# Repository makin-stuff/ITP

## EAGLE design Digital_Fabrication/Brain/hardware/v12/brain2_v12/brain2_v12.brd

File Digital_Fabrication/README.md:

This repo has all the design files, code, and documentation for [A Nervous System](https://www.priyankamakin.com/brain) by [Priyanka Makin](https://www.priyankamakin.com/)

# How to populate brain boards

For any version, each brain board consists of a string of 80 addressable LEDs , 40 on the front and 40 on the back. This is the only component used on the whole board which makes assembly pretty straight forward!

The addressable LED footprint used in this design was made to be used with [these NeoPixels I got from Adafruit.](https://www.adafruit.com/product/4957)

The orientation of the LED matters for the communication between LEDs to work, so always double-check before soldering!

If you are building up version 1.0 of these boards (with green soldermask) there is a white silkscreen triangle indicator for pin 1 on the LED footprint. Be sure to line this silkscreen up with the pin of the LED that also has a triangle cut out of it in the package.

For a more in-depth guide to surface mount soldering with solderpaste and a stencil, feel free to check out this [blog post](https://www.priyankamakin.com/blog/itp-thesis-i-this-system-is-nervous). Happy soldering!

<table class="table table-hover table-striped table-bordered">
  <tr align="center">
    <td></td>
    <td></td>
  </tr>
  <tr align="center">
    <td>Printed circuit board (v1.0) with silkscreen</td>
    <td>Adafruit NeoPixel</td>
  </tr>
</table>

# Note 08/19/24:

As I'm writing this ReadMe I'm realizing that I misnumbered the pins in the EAGLE footprint for the NeoPixel. This is just a notation error and doesn't affect functionality. Will update EAGLE library files in future revisions.

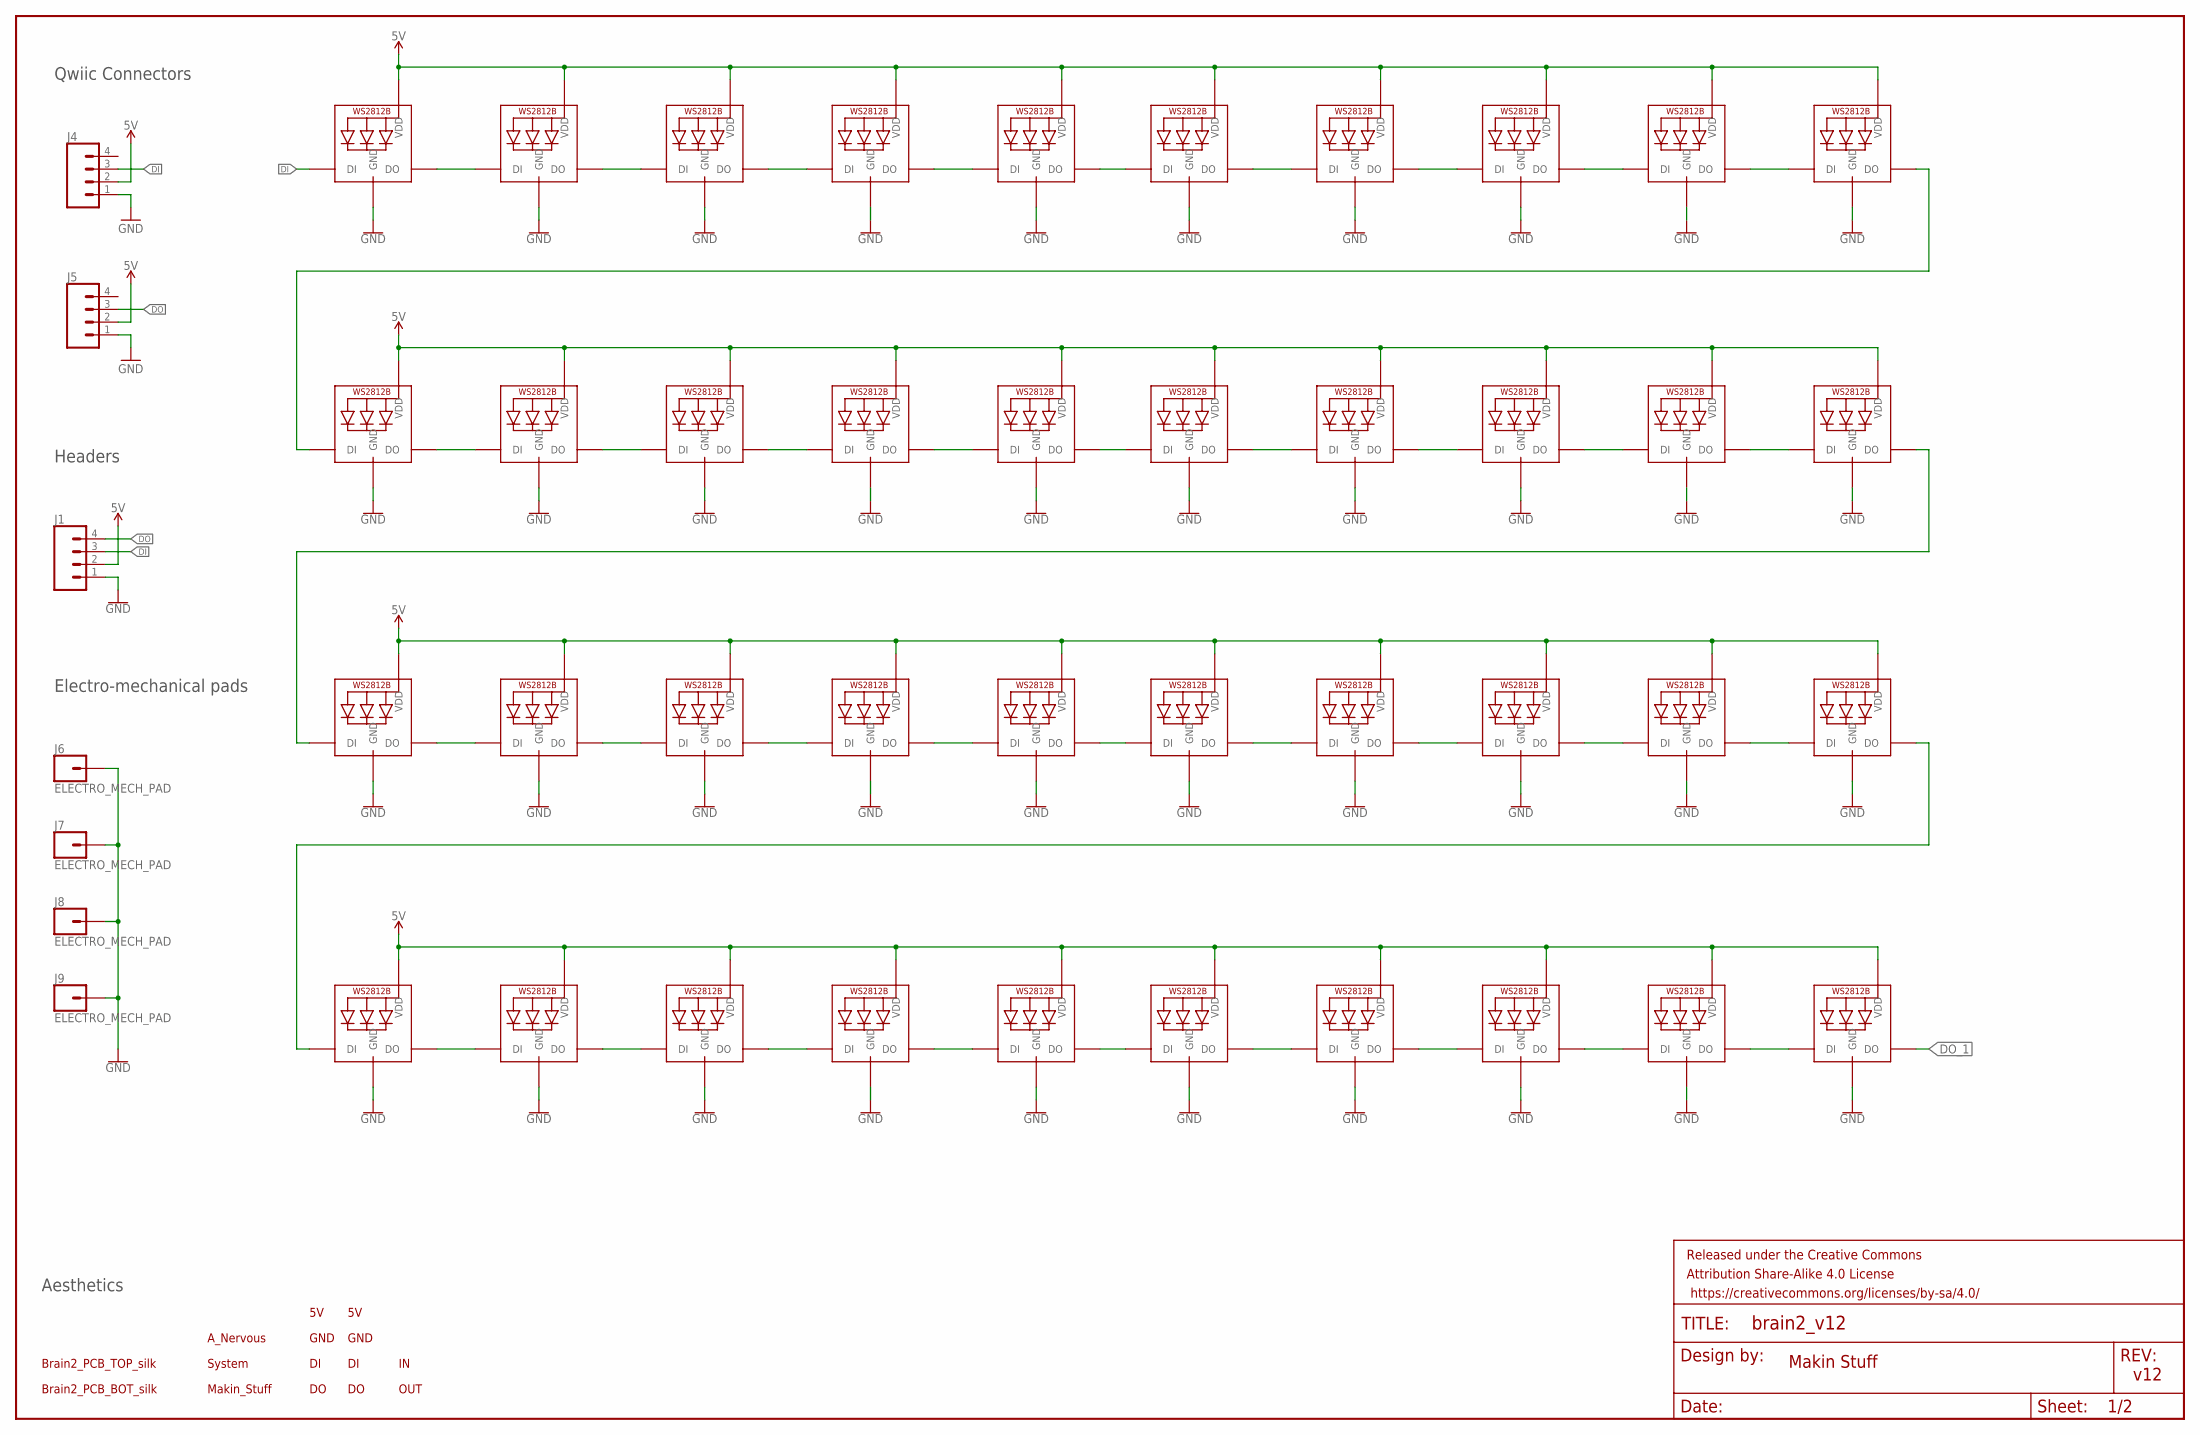
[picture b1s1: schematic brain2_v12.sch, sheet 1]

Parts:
FRAME2: FRAME-LEDGER; CREATIVE_COMMONS
J1: CONN_041X04_NO_SILK_NO_POP; 1X04_NO_SILK
J4, J5: CONN_04SMD3; JST04_1MM_RA
J6, J7, J8, J9: ELECTRO_MECH_PAD; 5X3_SOLDER_PAD
LED1, LED2, LED3, LED4, LED5, LED6, LED7, LED8, LED9, LED10, LED11, LED12, LED13, LED14, LED15, LED16, LED17, LED18, LED19, LED20, LED21, LED22, LED23, LED24, LED25, LED26, LED27, LED28, LED29, LED30, LED31, LED32, LED33, LED34, LED35, LED36, LED37, LED38, LED39, LED40: 3.5X3.5_RGB_LED3.5X3.5; 3.5X3.5_RGB_LED
U$1: A_NERVOUS0
U$2: SYSTEM1
U$3: MAKIN_STUFF2
U$4, U$5: 5V1
U$6, U$7: GND0
U$8, U$9: DI0
U$10, U$11: DO3
U$12: IN0
U$13: OUT1
U$14: BRAIN2_PCB_TOP_SILK
U$15: BRAIN2_PCB_BOT_SILK

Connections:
5V: J1.2, J4.2, J5.2, LED1.4 (VDD), LED2.4 (VDD), LED3.4 (VDD), LED4.4 (VDD), LED5.4 (VDD), LED6.4 (VDD), LED7.4 (VDD), LED8.4 (VDD), LED9.4 (VDD), LED10.4 (VDD), LED11.4 (VDD), LED12.4 (VDD), LED13.4 (VDD), LED14.4 (VDD), LED15.4 (VDD), LED16.4 (VDD), LED17.4 (VDD), LED18.4 (VDD), LED19.4 (VDD), LED20.4 (VDD), LED21.4 (VDD), LED22.4 (VDD), LED23.4 (VDD), LED24.4 (VDD), LED25.4 (VDD), LED26.4 (VDD), LED27.4 (VDD), LED28.4 (VDD), LED29.4 (VDD), LED30.4 (VDD), LED31.4 (VDD), LED32.4 (VDD), LED33.4 (VDD), LED34.4 (VDD), LED35.4 (VDD), LED36.4 (VDD), LED37.4 (VDD), LED38.4 (VDD), LED39.4 (VDD), LED40.4 (VDD); also elsewhere on the board
DI: J1.3, J4.3, LED1.3 (DI)
DO: J1.4, J5.3; also elsewhere on the board
DO_1: LED40.1 (DO); also elsewhere on the board
GND: J1.1, J4.1, J5.1, J6.P$1, J7.P$1, J8.P$1, J9.P$1, LED1.2 (GND), LED2.2 (GND), LED3.2 (GND), LED4.2 (GND), LED5.2 (GND), LED6.2 (GND), LED7.2 (GND), LED8.2 (GND), LED9.2 (GND), LED10.2 (GND), LED11.2 (GND), LED12.2 (GND), LED13.2 (GND), LED14.2 (GND), LED15.2 (GND), LED16.2 (GND), LED17.2 (GND), LED18.2 (GND), LED19.2 (GND), LED20.2 (GND), LED21.2 (GND), LED22.2 (GND), LED23.2 (GND), LED24.2 (GND), LED25.2 (GND), LED26.2 (GND), LED27.2 (GND), LED28.2 (GND), LED29.2 (GND), LED30.2 (GND), LED31.2 (GND), LED32.2 (GND), LED33.2 (GND), LED34.2 (GND), LED35.2 (GND), LED36.2 (GND), LED37.2 (GND), LED38.2 (GND), LED39.2 (GND), LED40.2 (GND); also elsewhere on the board
unnamed: LED1.1 (DO), LED2.3 (DI)
unnamed: LED2.1 (DO), LED3.3 (DI)
unnamed: LED3.1 (DO), LED4.3 (DI)
unnamed: LED4.1 (DO), LED5.3 (DI)
unnamed: LED6.1 (DO), LED7.3 (DI)
unnamed: LED7.1 (DO), LED8.3 (DI)
unnamed: LED8.1 (DO), LED9.3 (DI)
unnamed: LED9.1 (DO), LED10.3 (DI)
unnamed: LED11.1 (DO), LED12.3 (DI)
unnamed: LED5.1 (DO), LED6.3 (DI)
unnamed: LED12.1 (DO), LED13.3 (DI)
unnamed: LED13.1 (DO), LED14.3 (DI)
unnamed: LED14.1 (DO), LED15.3 (DI)
unnamed: LED16.1 (DO), LED17.3 (DI)
unnamed: LED17.1 (DO), LED18.3 (DI)
unnamed: LED18.1 (DO), LED19.3 (DI)
unnamed: LED19.1 (DO), LED20.3 (DI)
unnamed: LED15.1 (DO), LED16.3 (DI)
unnamed: LED21.1 (DO), LED22.3 (DI)
unnamed: LED22.1 (DO), LED23.3 (DI)
unnamed: LED23.1 (DO), LED24.3 (DI)
unnamed: LED24.1 (DO), LED25.3 (DI)
unnamed: LED26.1 (DO), LED27.3 (DI)
unnamed: LED27.1 (DO), LED28.3 (DI)
unnamed: LED28.1 (DO), LED29.3 (DI)
unnamed: LED29.1 (DO), LED30.3 (DI)
unnamed: LED25.1 (DO), LED26.3 (DI)
unnamed: LED31.1 (DO), LED32.3 (DI)
unnamed: LED32.1 (DO), LED33.3 (DI)
unnamed: LED33.1 (DO), LED34.3 (DI)
unnamed: LED34.1 (DO), LED35.3 (DI)
unnamed: LED36.1 (DO), LED37.3 (DI)
unnamed: LED37.1 (DO), LED38.3 (DI)
unnamed: LED38.1 (DO), LED39.3 (DI)
unnamed: LED39.1 (DO), LED40.3 (DI)
unnamed: LED35.1 (DO), LED36.3 (DI)
unnamed: LED10.1 (DO), LED11.3 (DI)
unnamed: LED20.1 (DO), LED21.3 (DI)
unnamed: LED30.1 (DO), LED31.3 (DI)

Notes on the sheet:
Makin Stuff
v12
Qwiic Connectors
Headers
Electro-mechanical pads
Aesthetics

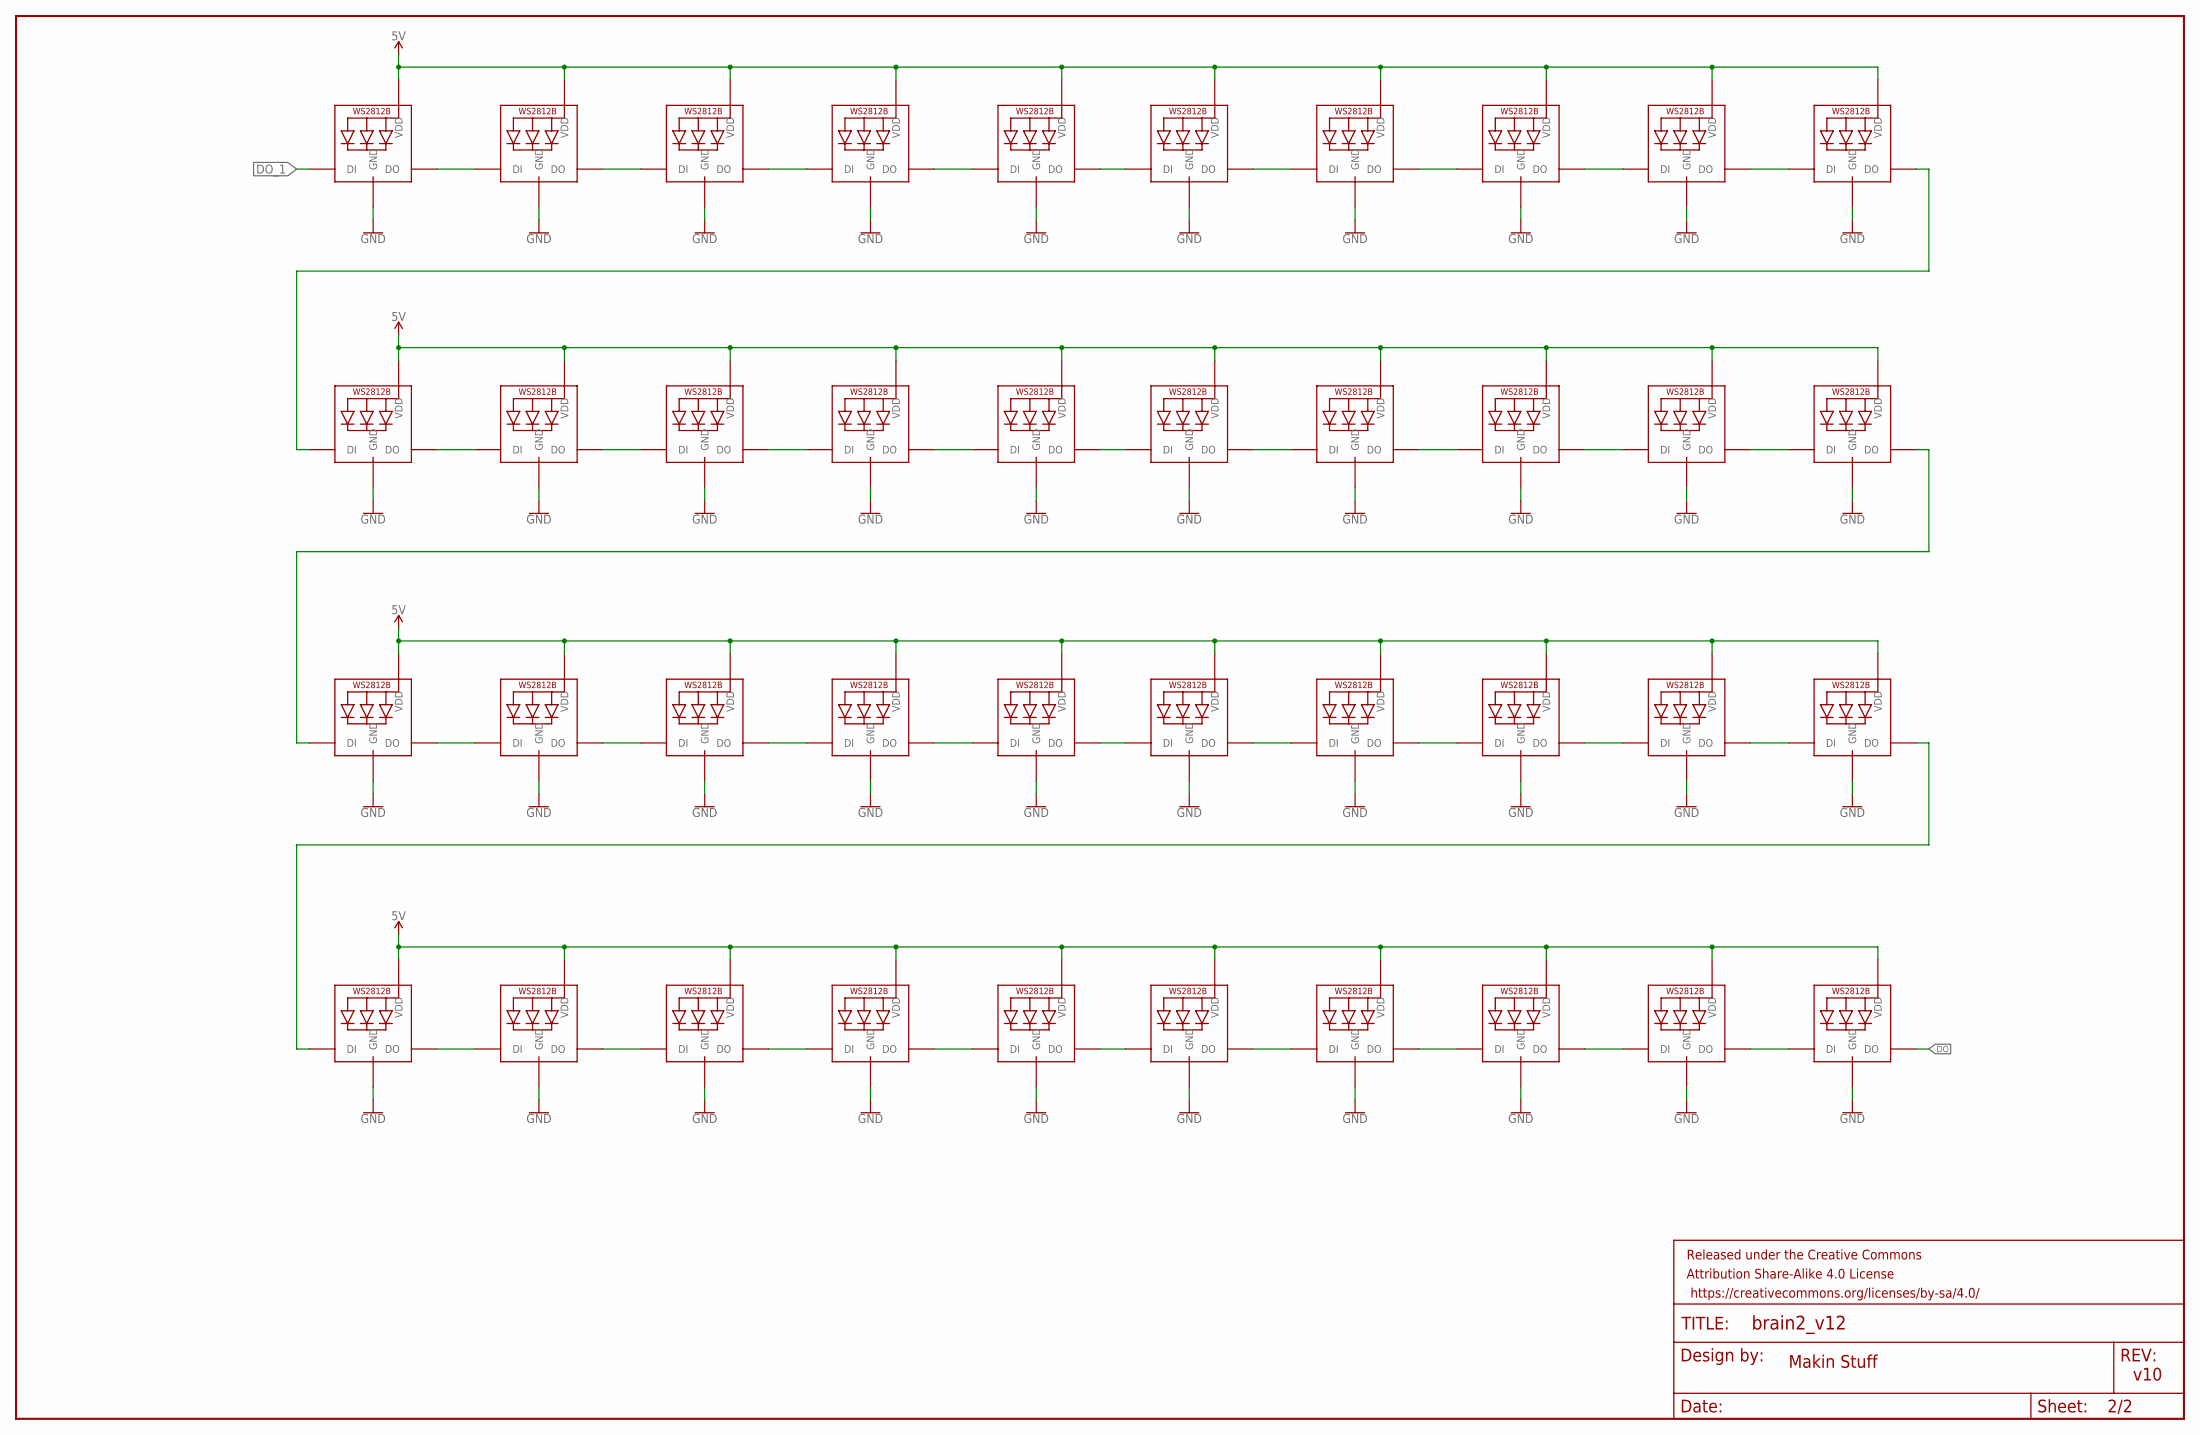
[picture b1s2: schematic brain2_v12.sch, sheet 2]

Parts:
FRAME1, FRAME3: FRAME-LEDGER; CREATIVE_COMMONS
LED41, LED42, LED43, LED44, LED45, LED46, LED47, LED48, LED49, LED50, LED51, LED52, LED53, LED54, LED55, LED56, LED57, LED58, LED59, LED60, LED61, LED62, LED63, LED64, LED65, LED66, LED67, LED68, LED69, LED70, LED71, LED72, LED73, LED74, LED75, LED76, LED77, LED78, LED79, LED80: 3.5X3.5_RGB_LED3.5X3.5; 3.5X3.5_RGB_LED

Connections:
5V: LED41.4 (VDD), LED42.4 (VDD), LED43.4 (VDD), LED44.4 (VDD), LED45.4 (VDD), LED46.4 (VDD), LED47.4 (VDD), LED48.4 (VDD), LED49.4 (VDD), LED50.4 (VDD), LED51.4 (VDD), LED52.4 (VDD), LED53.4 (VDD), LED54.4 (VDD), LED55.4 (VDD), LED56.4 (VDD), LED57.4 (VDD), LED58.4 (VDD), LED59.4 (VDD), LED60.4 (VDD), LED61.4 (VDD), LED62.4 (VDD), LED63.4 (VDD), LED64.4 (VDD), LED65.4 (VDD), LED66.4 (VDD), LED67.4 (VDD), LED68.4 (VDD), LED69.4 (VDD), LED70.4 (VDD), LED71.4 (VDD), LED72.4 (VDD), LED73.4 (VDD), LED74.4 (VDD), LED75.4 (VDD), LED76.4 (VDD), LED77.4 (VDD), LED78.4 (VDD), LED79.4 (VDD), LED80.4 (VDD); also elsewhere on the board
DO: LED80.1 (DO); also elsewhere on the board
DO_1: LED41.3 (DI); also elsewhere on the board
GND: LED41.2 (GND), LED42.2 (GND), LED43.2 (GND), LED44.2 (GND), LED45.2 (GND), LED46.2 (GND), LED47.2 (GND), LED48.2 (GND), LED49.2 (GND), LED50.2 (GND), LED51.2 (GND), LED52.2 (GND), LED53.2 (GND), LED54.2 (GND), LED55.2 (GND), LED56.2 (GND), LED57.2 (GND), LED58.2 (GND), LED59.2 (GND), LED60.2 (GND), LED61.2 (GND), LED62.2 (GND), LED63.2 (GND), LED64.2 (GND), LED65.2 (GND), LED66.2 (GND), LED67.2 (GND), LED68.2 (GND), LED69.2 (GND), LED70.2 (GND), LED71.2 (GND), LED72.2 (GND), LED73.2 (GND), LED74.2 (GND), LED75.2 (GND), LED76.2 (GND), LED77.2 (GND), LED78.2 (GND), LED79.2 (GND), LED80.2 (GND); also elsewhere on the board
unnamed: LED41.1 (DO), LED42.3 (DI)
unnamed: LED42.1 (DO), LED43.3 (DI)
unnamed: LED43.1 (DO), LED44.3 (DI)
unnamed: LED44.1 (DO), LED45.3 (DI)
unnamed: LED46.1 (DO), LED47.3 (DI)
unnamed: LED47.1 (DO), LED48.3 (DI)
unnamed: LED48.1 (DO), LED49.3 (DI)
unnamed: LED49.1 (DO), LED50.3 (DI)
unnamed: LED45.1 (DO), LED46.3 (DI)
unnamed: LED51.1 (DO), LED52.3 (DI)
unnamed: LED52.1 (DO), LED53.3 (DI)
unnamed: LED53.1 (DO), LED54.3 (DI)
unnamed: LED54.1 (DO), LED55.3 (DI)
unnamed: LED56.1 (DO), LED57.3 (DI)
unnamed: LED57.1 (DO), LED58.3 (DI)
unnamed: LED58.1 (DO), LED59.3 (DI)
unnamed: LED59.1 (DO), LED60.3 (DI)
unnamed: LED55.1 (DO), LED56.3 (DI)
unnamed: LED61.1 (DO), LED62.3 (DI)
unnamed: LED62.1 (DO), LED63.3 (DI)
unnamed: LED63.1 (DO), LED64.3 (DI)
unnamed: LED64.1 (DO), LED65.3 (DI)
unnamed: LED66.1 (DO), LED67.3 (DI)
unnamed: LED67.1 (DO), LED68.3 (DI)
unnamed: LED68.1 (DO), LED69.3 (DI)
unnamed: LED69.1 (DO), LED70.3 (DI)
unnamed: LED65.1 (DO), LED66.3 (DI)
unnamed: LED71.1 (DO), LED72.3 (DI)
unnamed: LED72.1 (DO), LED73.3 (DI)
unnamed: LED73.1 (DO), LED74.3 (DI)
unnamed: LED74.1 (DO), LED75.3 (DI)
unnamed: LED76.1 (DO), LED77.3 (DI)
unnamed: LED77.1 (DO), LED78.3 (DI)
unnamed: LED78.1 (DO), LED79.3 (DI)
unnamed: LED79.1 (DO), LED80.3 (DI)
unnamed: LED75.1 (DO), LED76.3 (DI)
unnamed: LED50.1 (DO), LED51.3 (DI)
unnamed: LED60.1 (DO), LED61.3 (DI)
unnamed: LED70.1 (DO), LED71.3 (DI)

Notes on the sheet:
Makin Stuff
v10

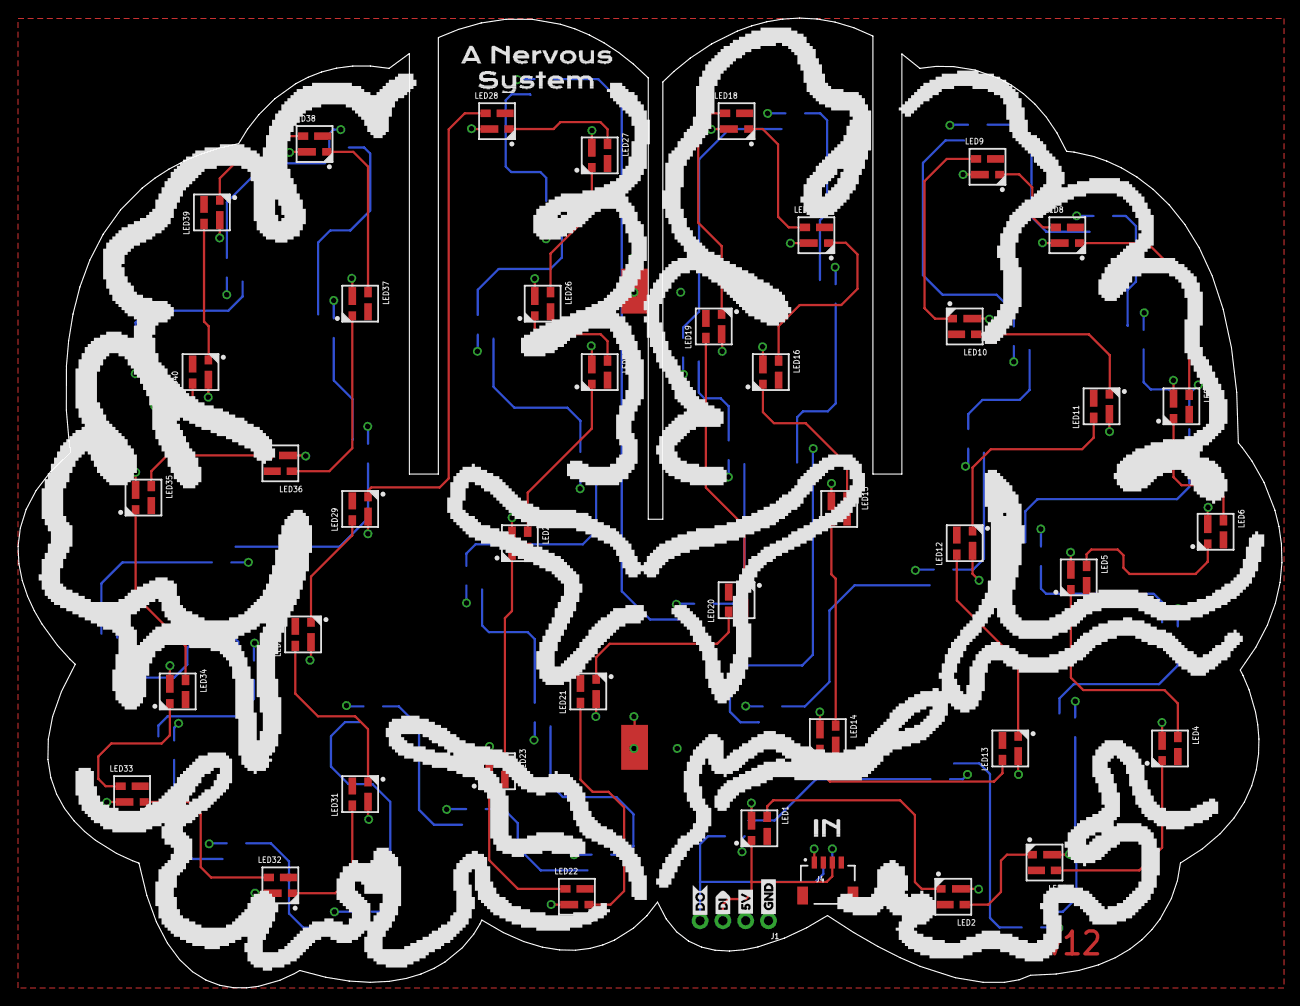
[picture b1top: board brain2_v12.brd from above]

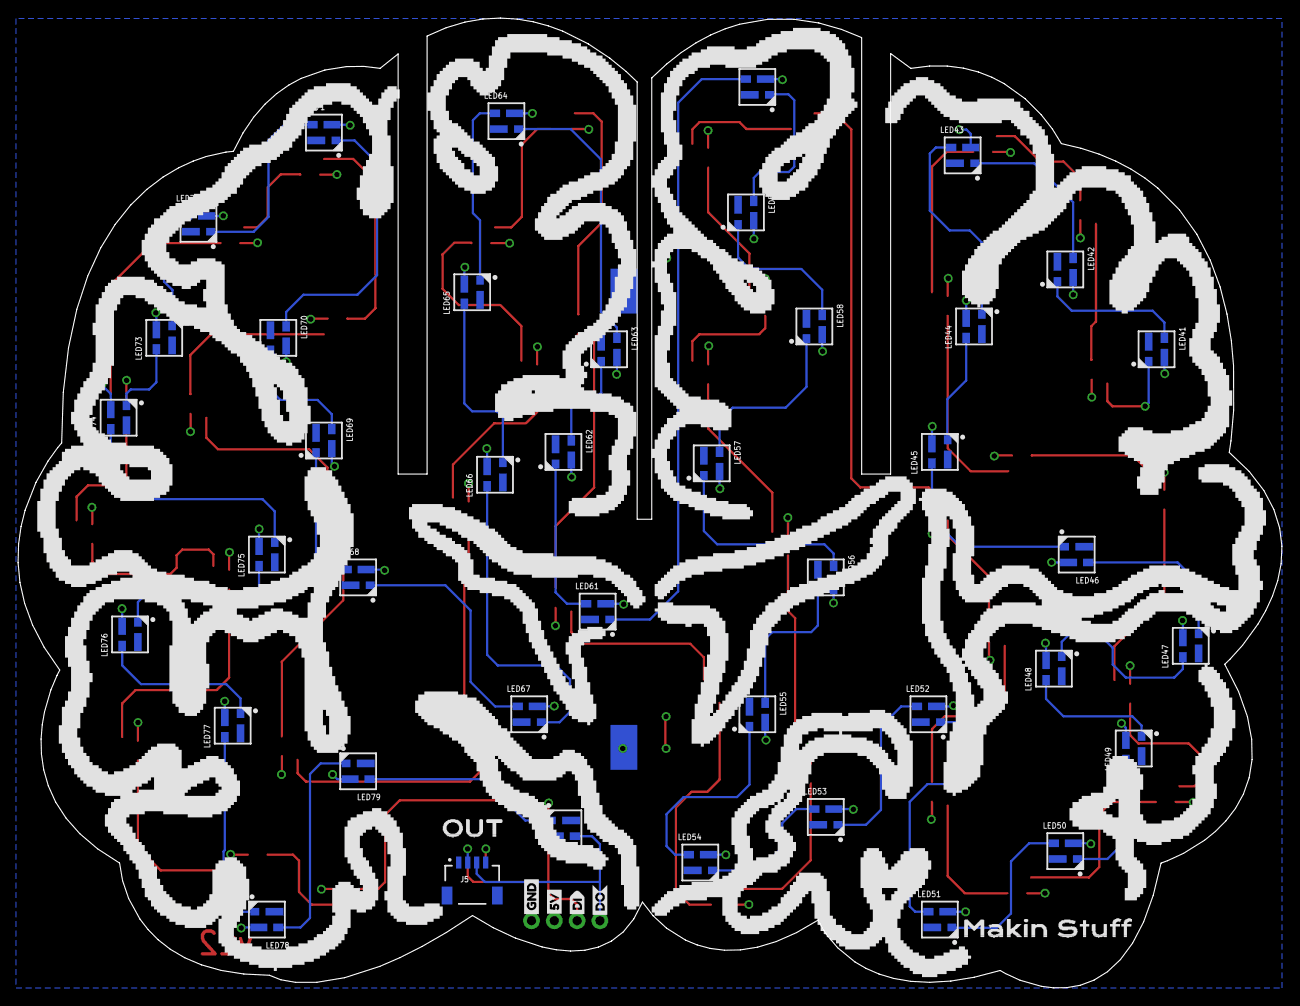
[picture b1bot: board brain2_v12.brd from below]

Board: 2 copper layers, 140.7 x 108.0 mm, 105 parts (50 on the bottom side), 83 nets.

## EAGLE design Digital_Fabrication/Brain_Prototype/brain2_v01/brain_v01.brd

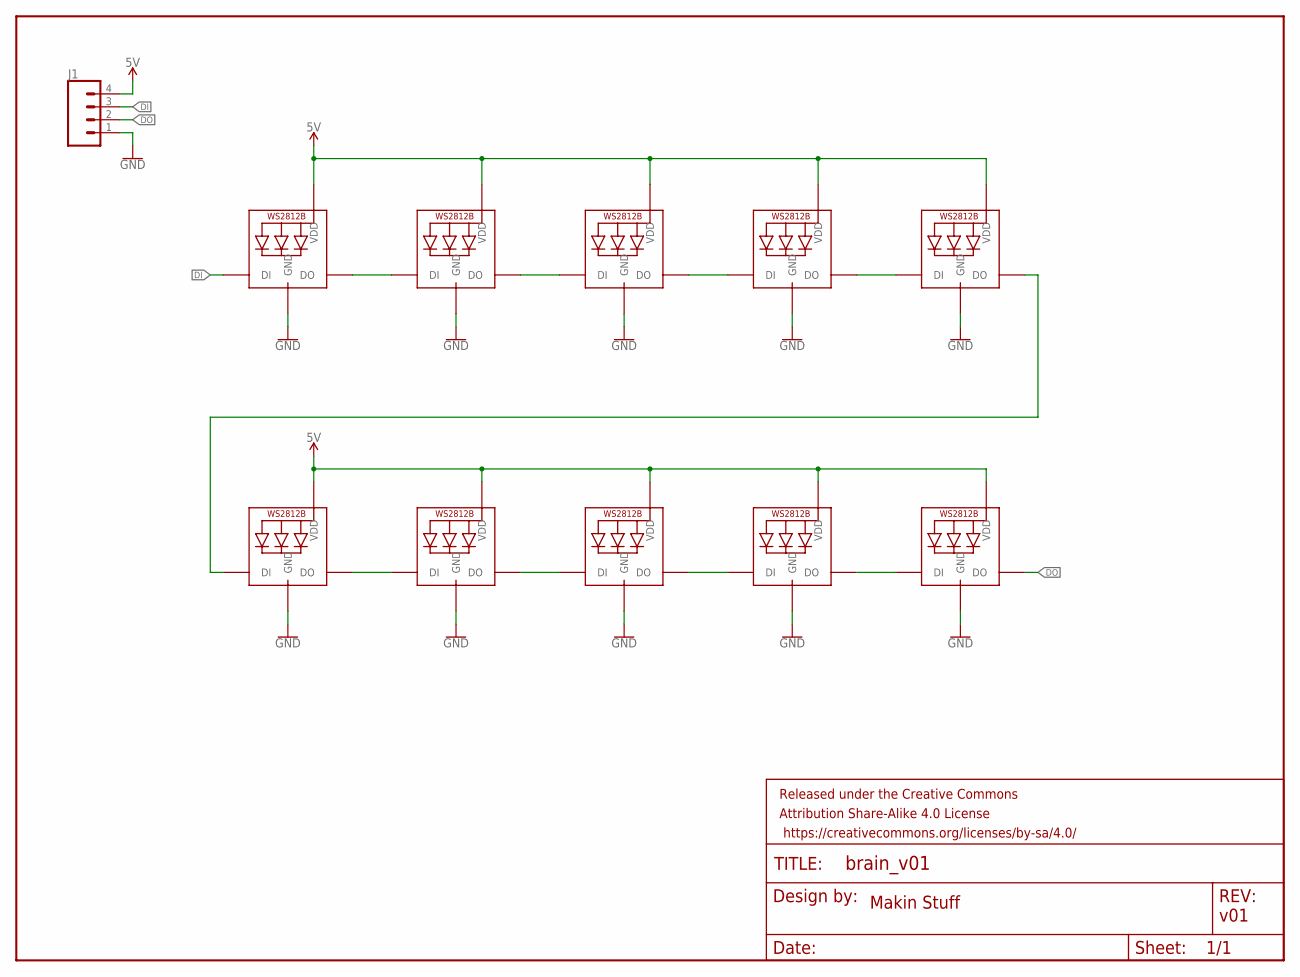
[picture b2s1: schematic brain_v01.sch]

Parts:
FRAME1: FRAME-LETTER; CREATIVE_COMMONS
J1: CONN_04PTH; 1X04
LED1, LED2, LED3, LED4, LED5, LED6, LED7, LED8, LED9, LED10: WS2812B3535; LED3535

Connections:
5V: J1.4, LED1.2 (VDD), LED2.2 (VDD), LED3.2 (VDD), LED4.2 (VDD), LED5.2 (VDD), LED6.2 (VDD), LED7.2 (VDD), LED8.2 (VDD), LED9.2 (VDD), LED10.2 (VDD)
DI: J1.3, LED1.1 (DI)
DO: J1.2, LED10.3 (DO)
GND: J1.1, LED1.4 (GND), LED2.4 (GND), LED3.4 (GND), LED4.4 (GND), LED5.4 (GND), LED6.4 (GND), LED7.4 (GND), LED8.4 (GND), LED9.4 (GND), LED10.4 (GND)
unnamed: LED1.3 (DO), LED2.1 (DI)
unnamed: LED2.3 (DO), LED3.1 (DI)
unnamed: LED3.3 (DO), LED4.1 (DI)
unnamed: LED4.3 (DO), LED5.1 (DI)
unnamed: LED6.3 (DO), LED7.1 (DI)
unnamed: LED7.3 (DO), LED8.1 (DI)
unnamed: LED8.3 (DO), LED9.1 (DI)
unnamed: LED9.3 (DO), LED10.1 (DI)
unnamed: LED5.3 (DO), LED6.1 (DI)

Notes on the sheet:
Makin Stuff
v01

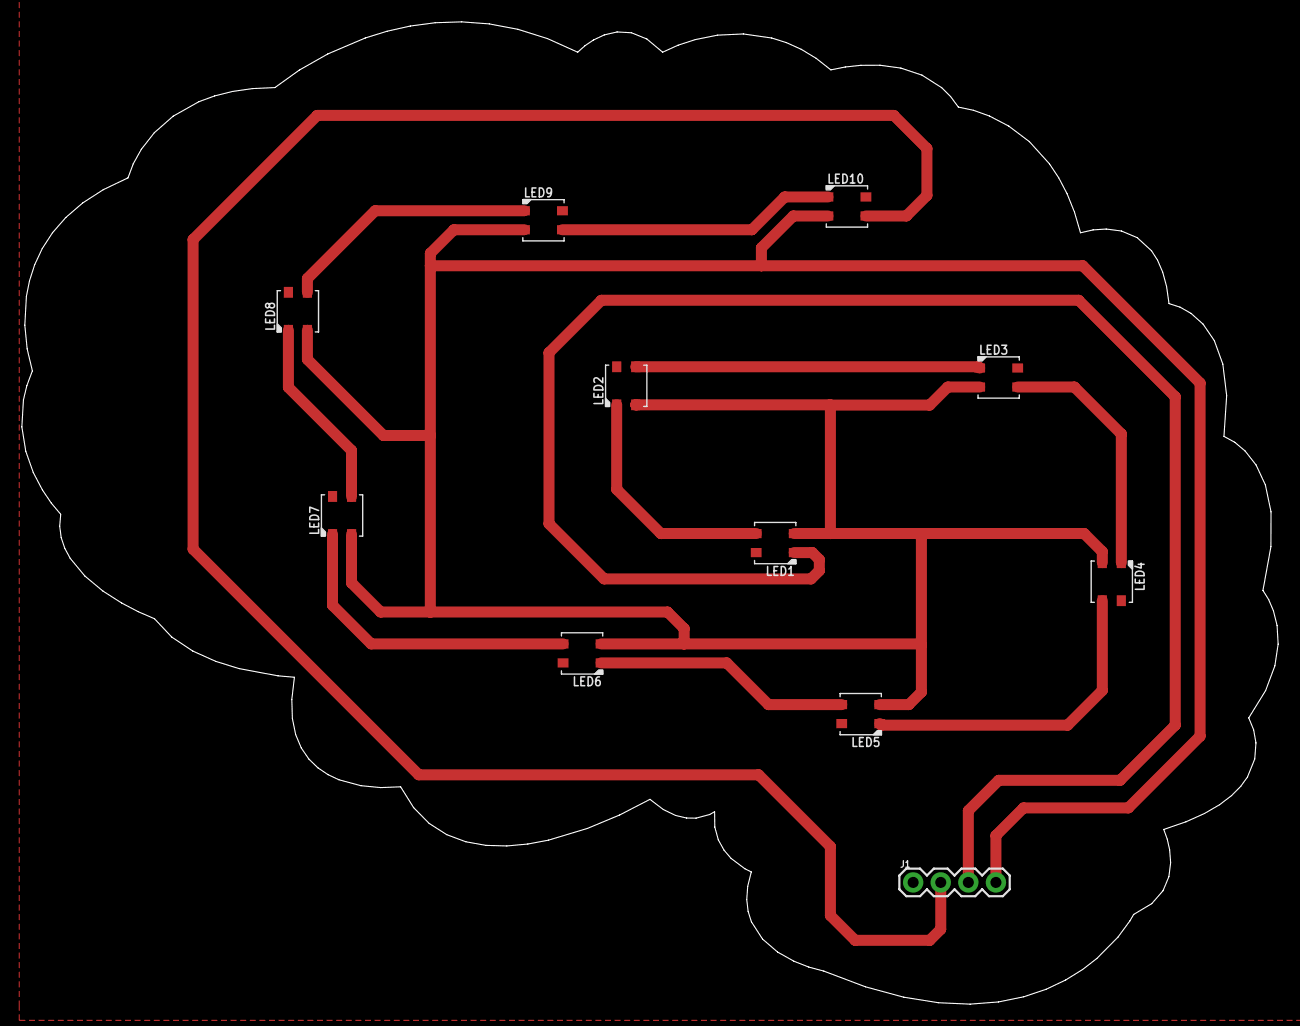
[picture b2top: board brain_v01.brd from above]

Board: 2 copper layers, 115.7 x 90.4 mm, 12 parts (0 on the bottom side), 13 nets.

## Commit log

2022-09-10 Add sound files for scavenger hunt
2022-09-21 Add sound vacation to repo
2022-10-09 Commit networked game controller code
2022-11-13 Add textile interfaces code
    For single button and force sensor
2022-11-17 Add v2.0 code to repo
    Using new encoder library https://github.com/M-Reimer/EncoderStepCounter
2022-11-17 Revert "Add v2.0 code to repo"
    This reverts commit 2f2a05a08a557c0a43f54c5d0638a03851926795.
2022-11-18 Add MQTT project to repo
2022-11-18 Rename "Understanding Networks" folder because terminal does not like spaces!
2022-11-21 Add "initiation" nodejs microservice example
2022-11-23 Update MQTT Node File Writer
2023-02-22 Add v01 of device dashboard to github
2023-02-22 Rename repo by removing spaces
2023-02-22 Public folder
    Add all webpage files into a "public" folder. Create server.js and package.json
2023-03-07 Add the OLED code
2023-03-07 Whoops
2023-03-07 Add laser cutter files
2023-04-10 Add Hue_Control repo
2023-11-05 Commit bots and brain
    * Two Discord bots for Program A2Z, scream machine and scaredy bot
    * Prototype for brain PCB in Eagle
2023-11-05 Remove
2023-11-05 hello
2023-11-07 Create footprint for LED, v02 of board
2023-11-08 Add v02 eagle prototype
    Add neopixel test code
2023-11-30 brain v10
2023-12-01 brain 2 v10!
2023-12-01 generate gerbers
2023-12-17 some stuff
2024-01-30 v11 hardware revision
    updates:
    * added orientation indicators to LED footprint
    * added qwiic connectors to connect between brain boards easier
    * added through holes for because
    * added more + bigger pads for electro mechanical connection between brain boards
2024-01-31 Add silkscreen
2024-02-04 brain boards v11
    Added custom silkscreen
2024-02-06 reorganize structure
2024-02-28 update strandtest sketches for brain debug
2024-03-20 Create brain v12
    Fixed short created by the pads used for electromechanical connection!
2024-04-07 reorganize software
2024-04-17 Add washing machine!
2024-05-06 add interFACE code
2024-08-13 Update code for sample sequencer
2024-08-20 Add pics for readme to brain repo
2024-10-25 Push most recent interface code
2024-10-25 Change folder name from code to software. Add design files
2024-10-26 Add system diagrams

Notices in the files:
parts and their libraries:
SparkFun-Aesthetics: Licensing: Creative Commons ShareAlike 4.0 International - https://creativecommons.org/licenses/by-sa/4.0
SparkFun-Aesthetics: Released under the Creative Commons Attribution Share-Alike 4.0 License
SparkFun-Aesthetics: https://creativecommons.org/licenses/by-sa/4.0
